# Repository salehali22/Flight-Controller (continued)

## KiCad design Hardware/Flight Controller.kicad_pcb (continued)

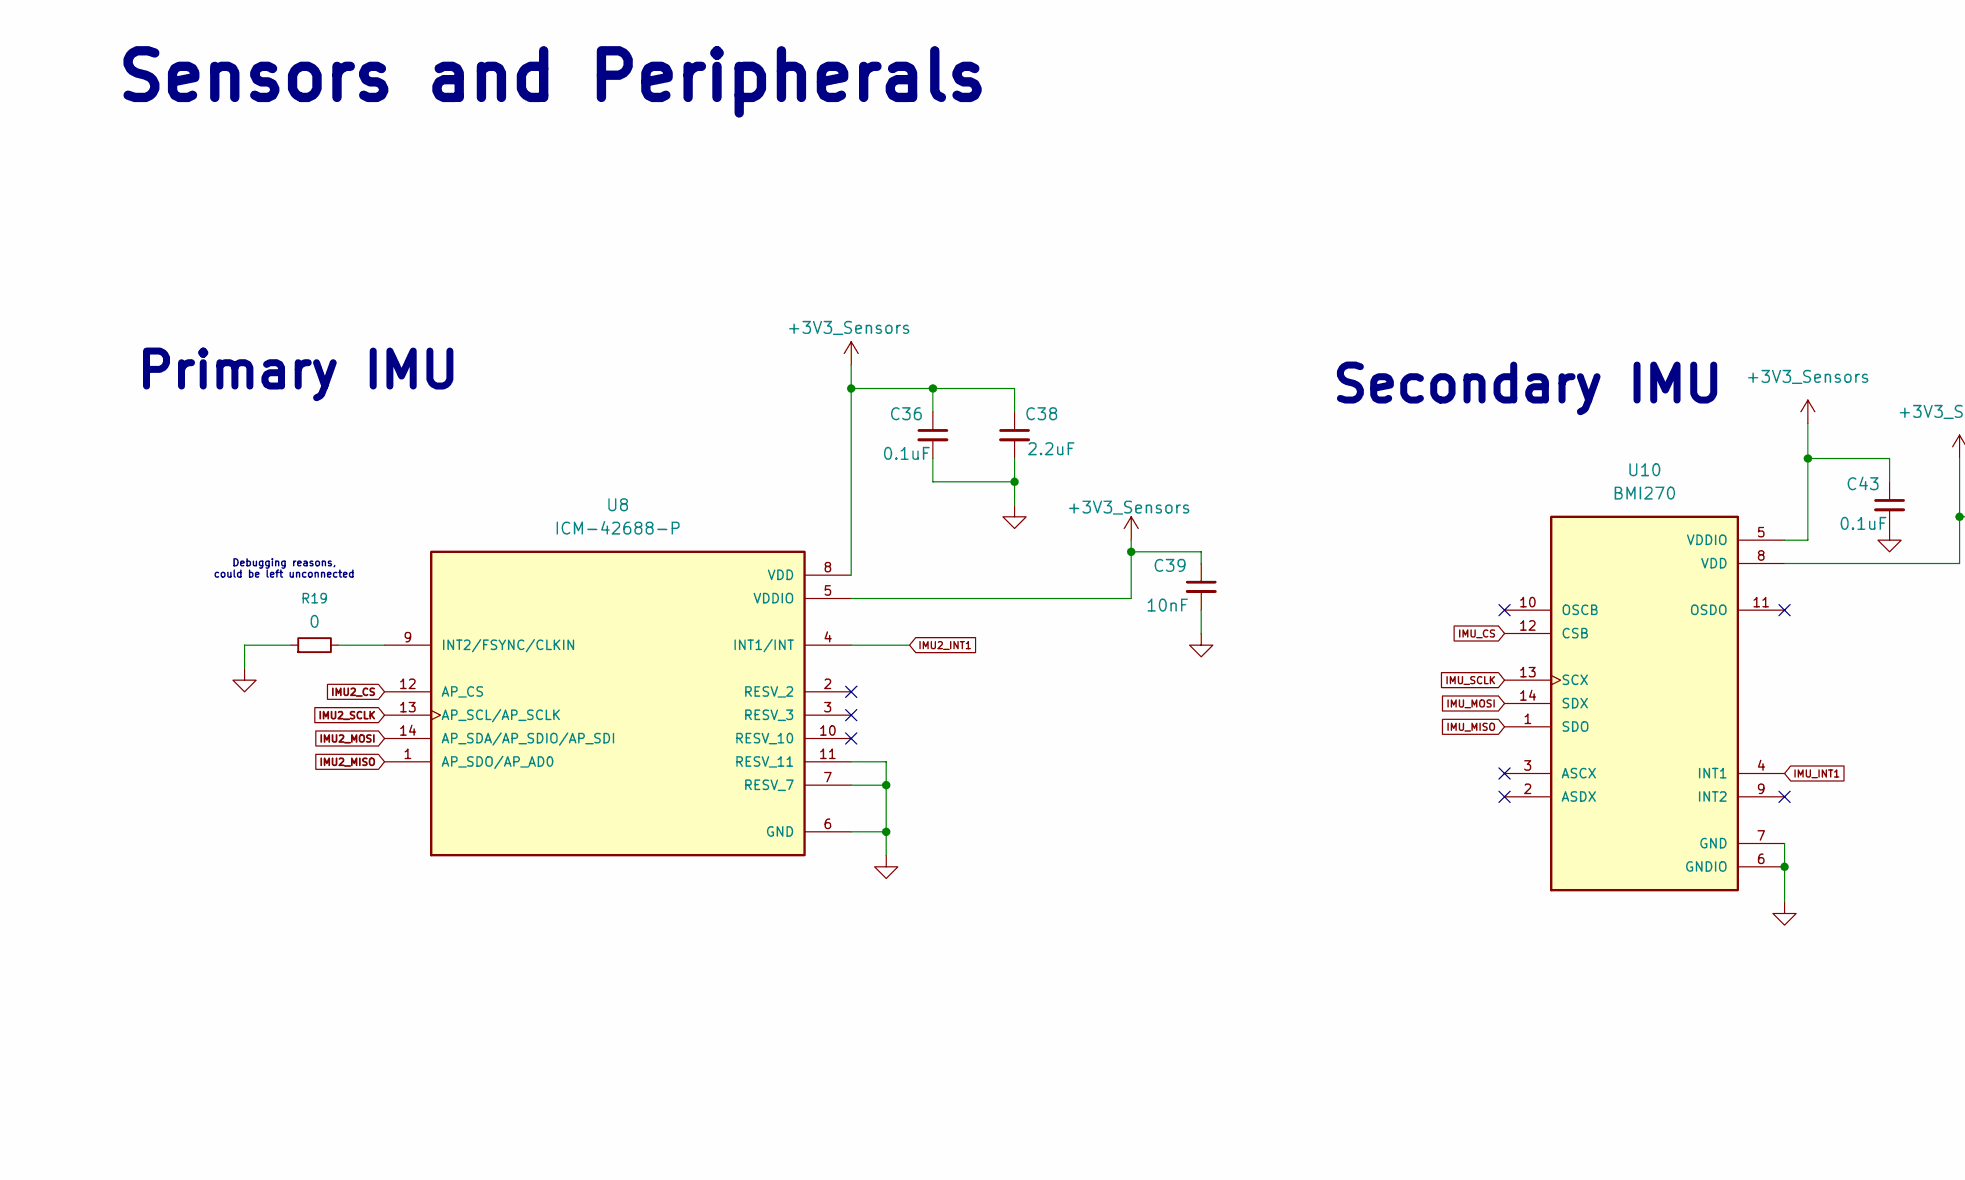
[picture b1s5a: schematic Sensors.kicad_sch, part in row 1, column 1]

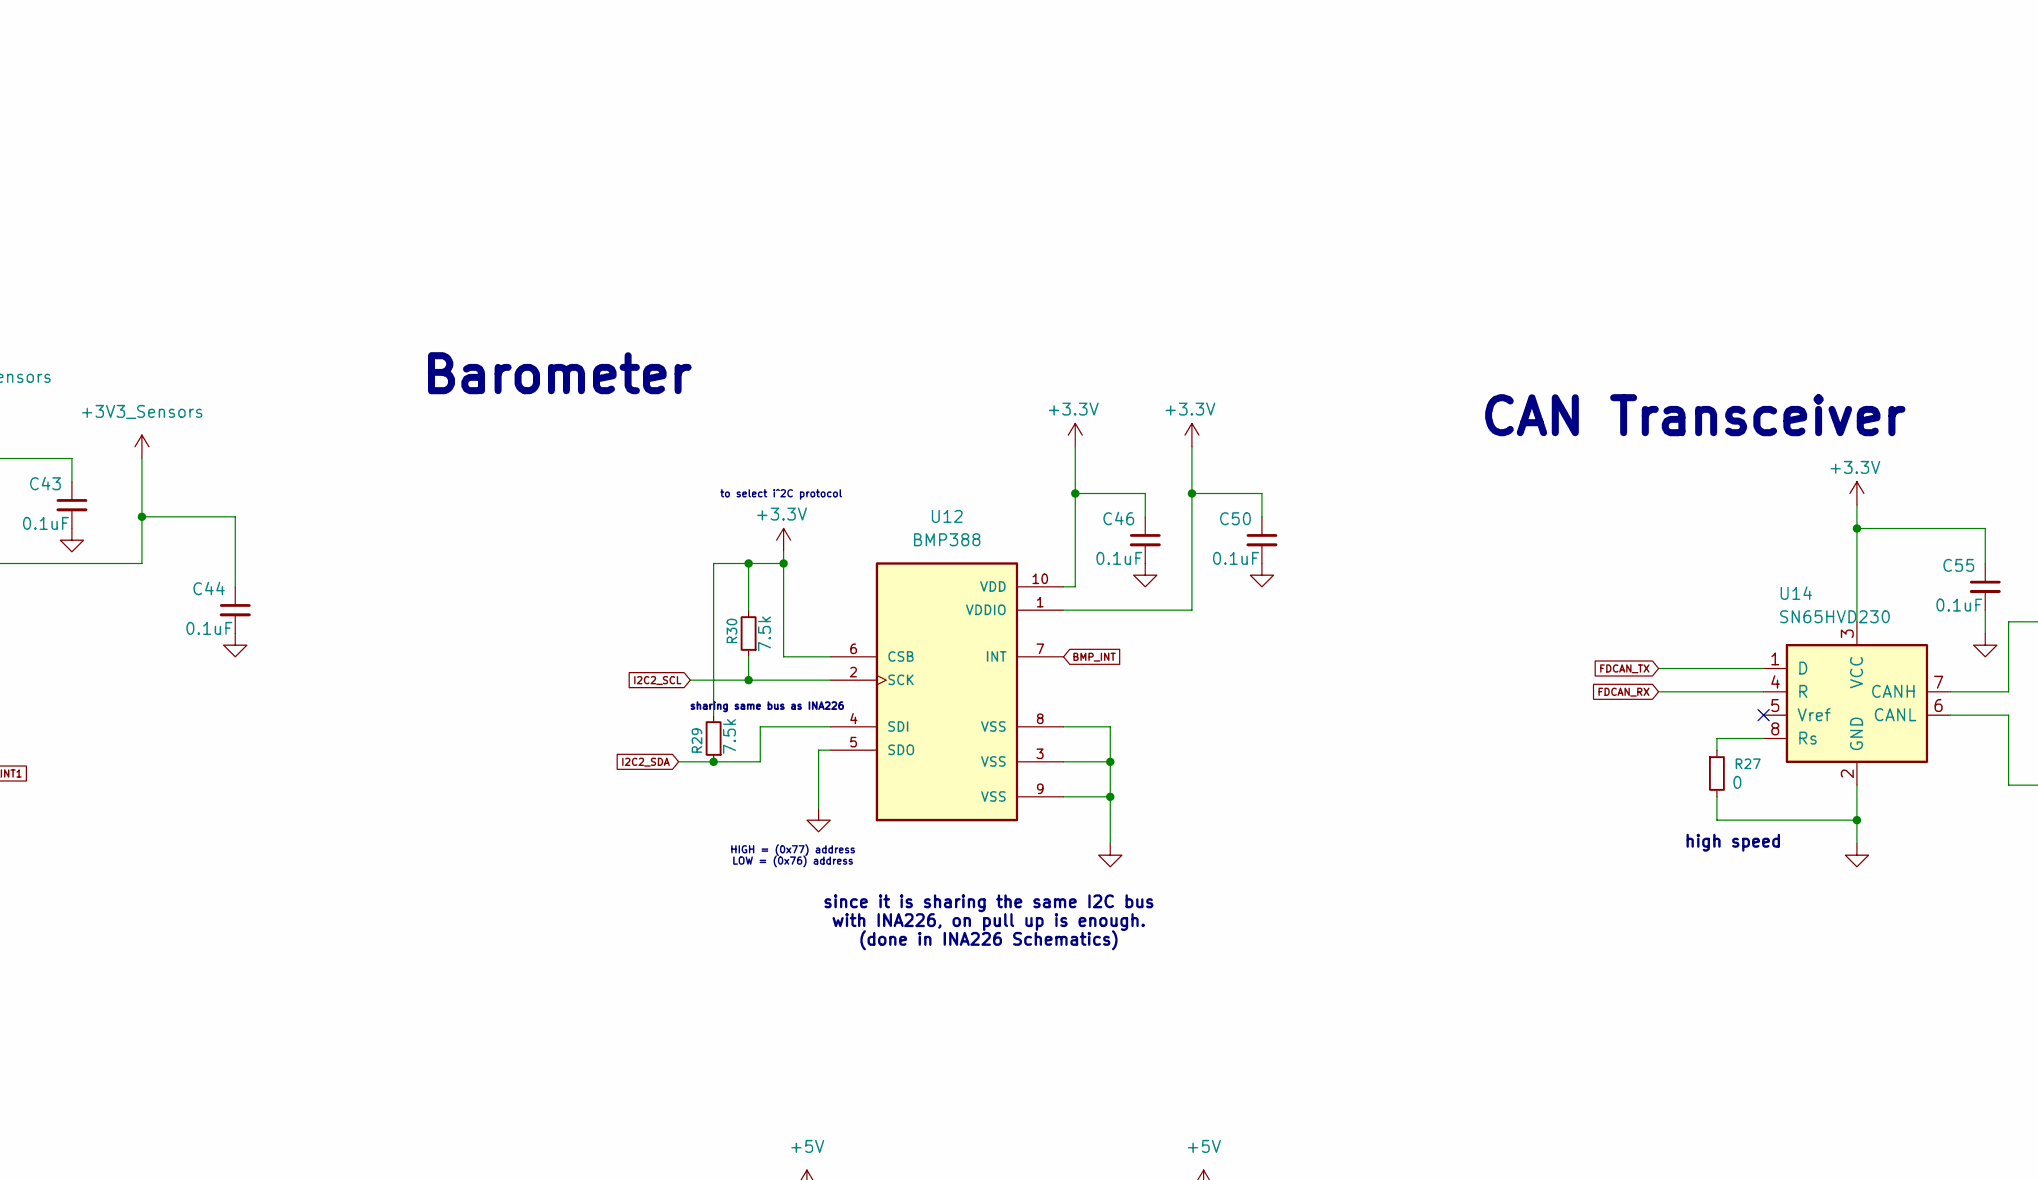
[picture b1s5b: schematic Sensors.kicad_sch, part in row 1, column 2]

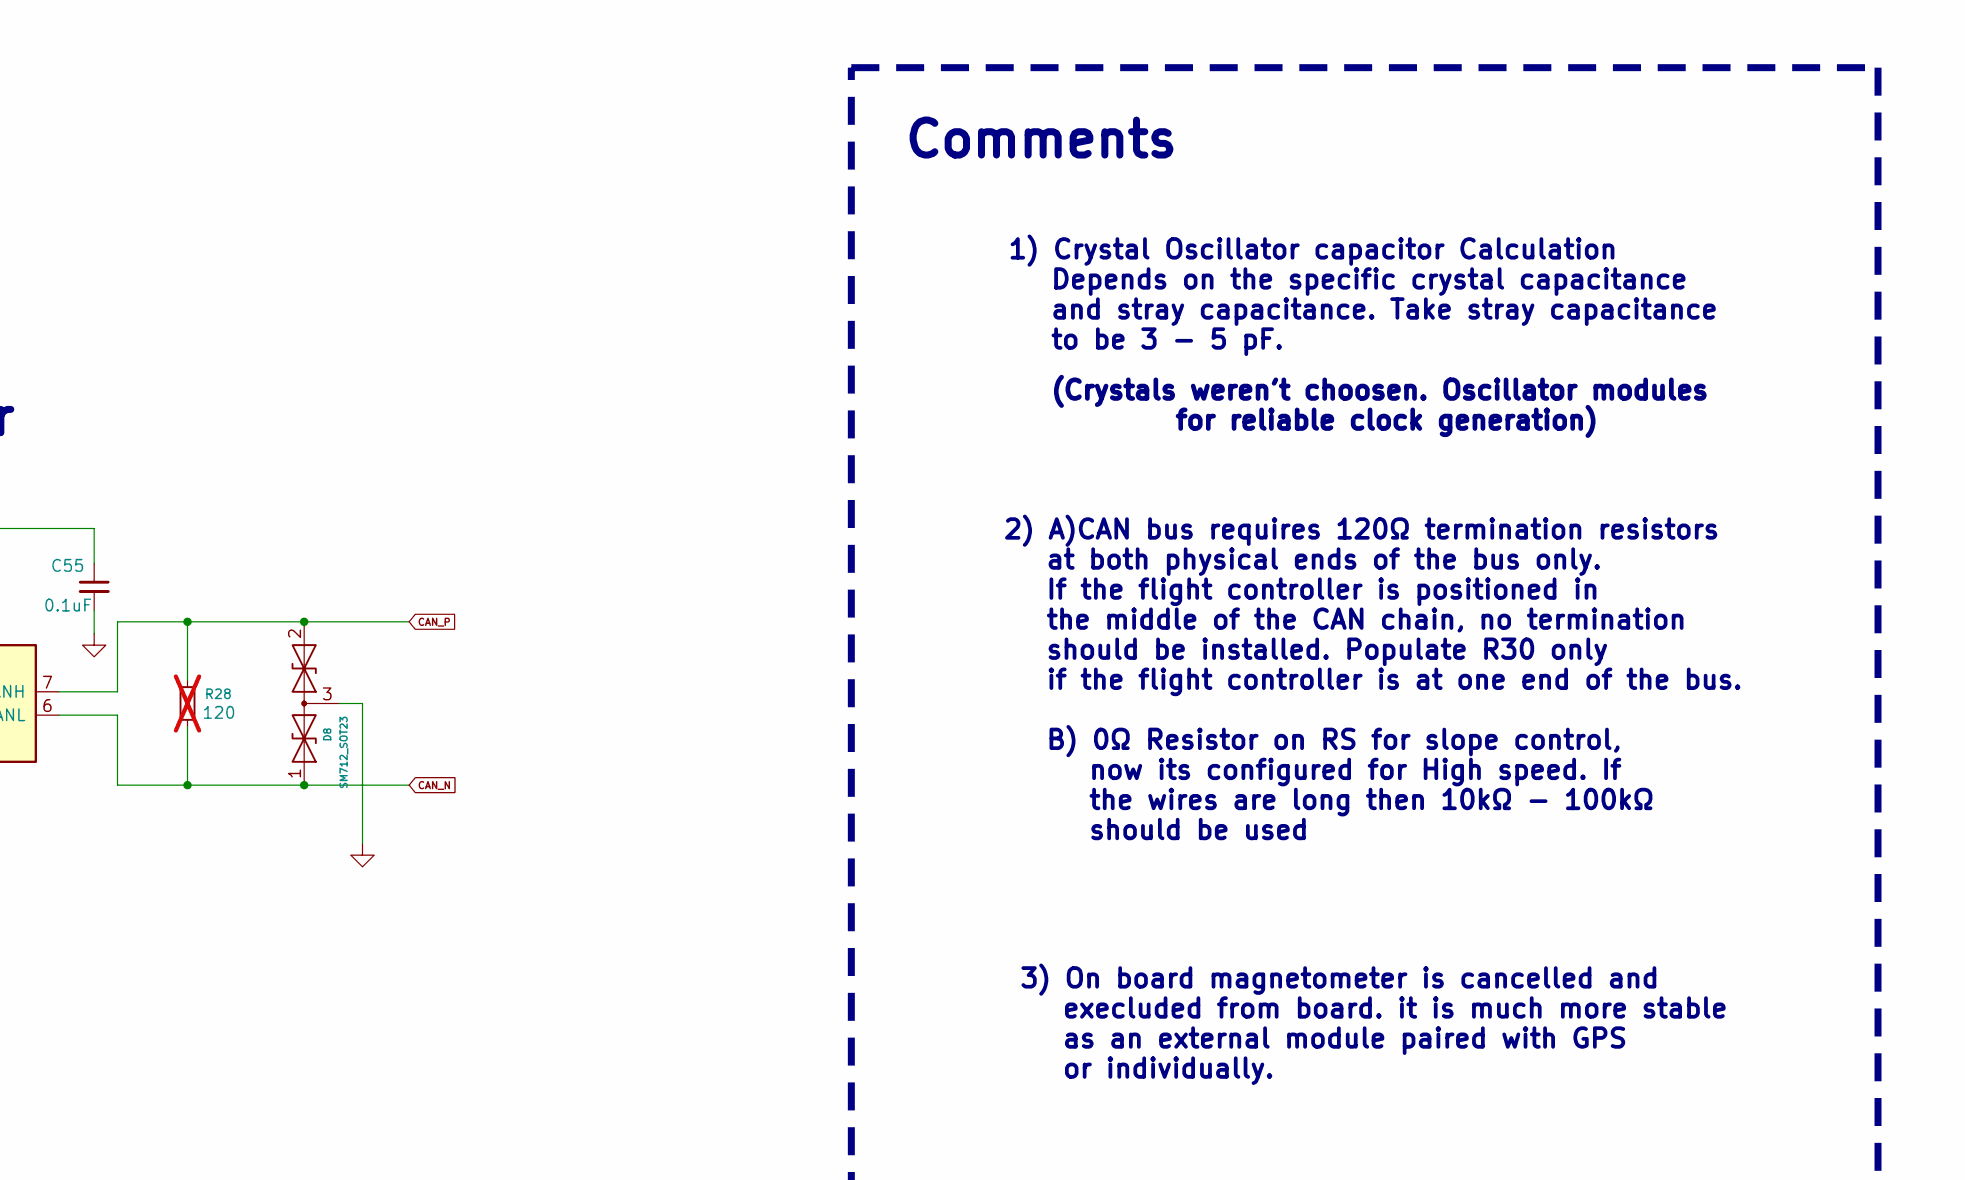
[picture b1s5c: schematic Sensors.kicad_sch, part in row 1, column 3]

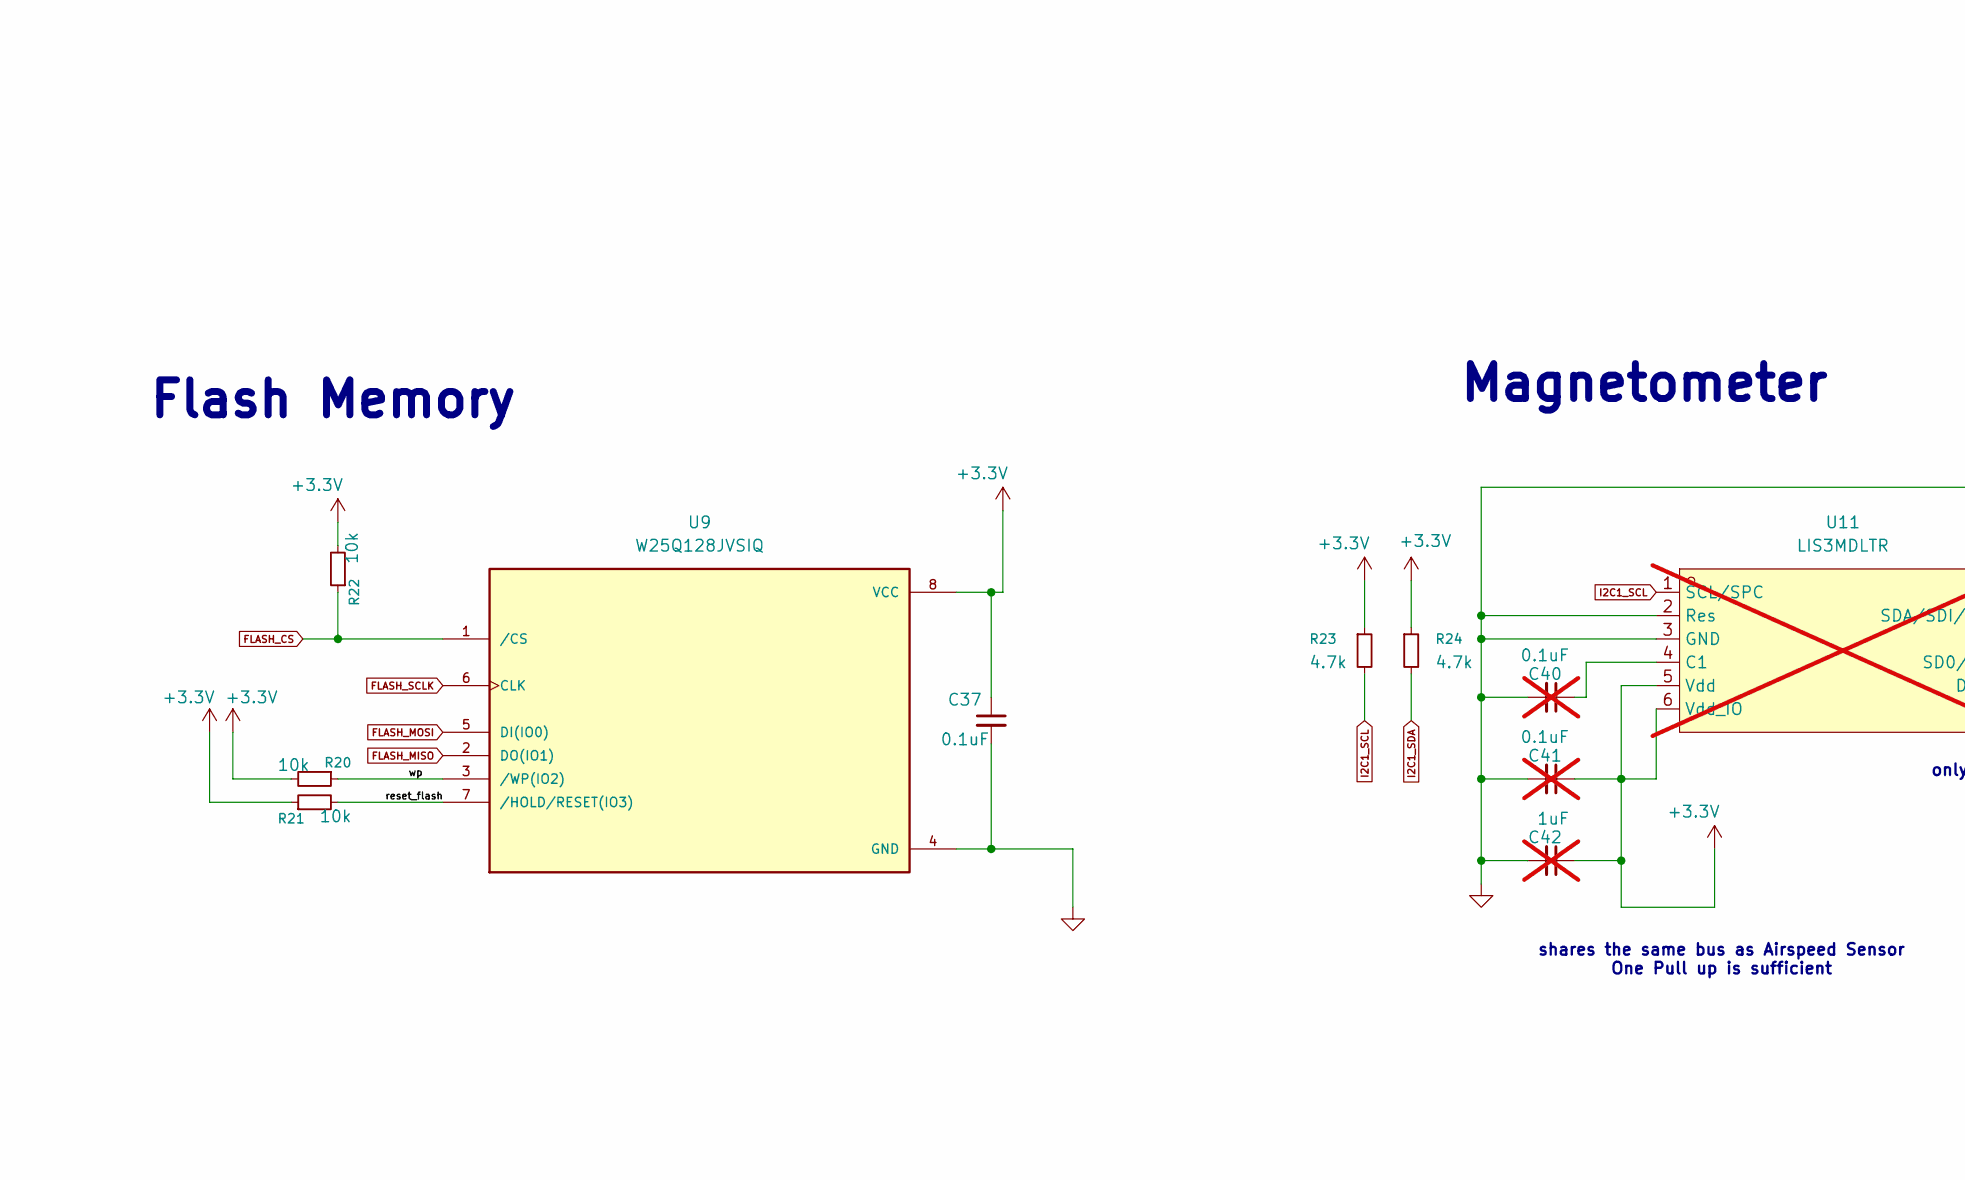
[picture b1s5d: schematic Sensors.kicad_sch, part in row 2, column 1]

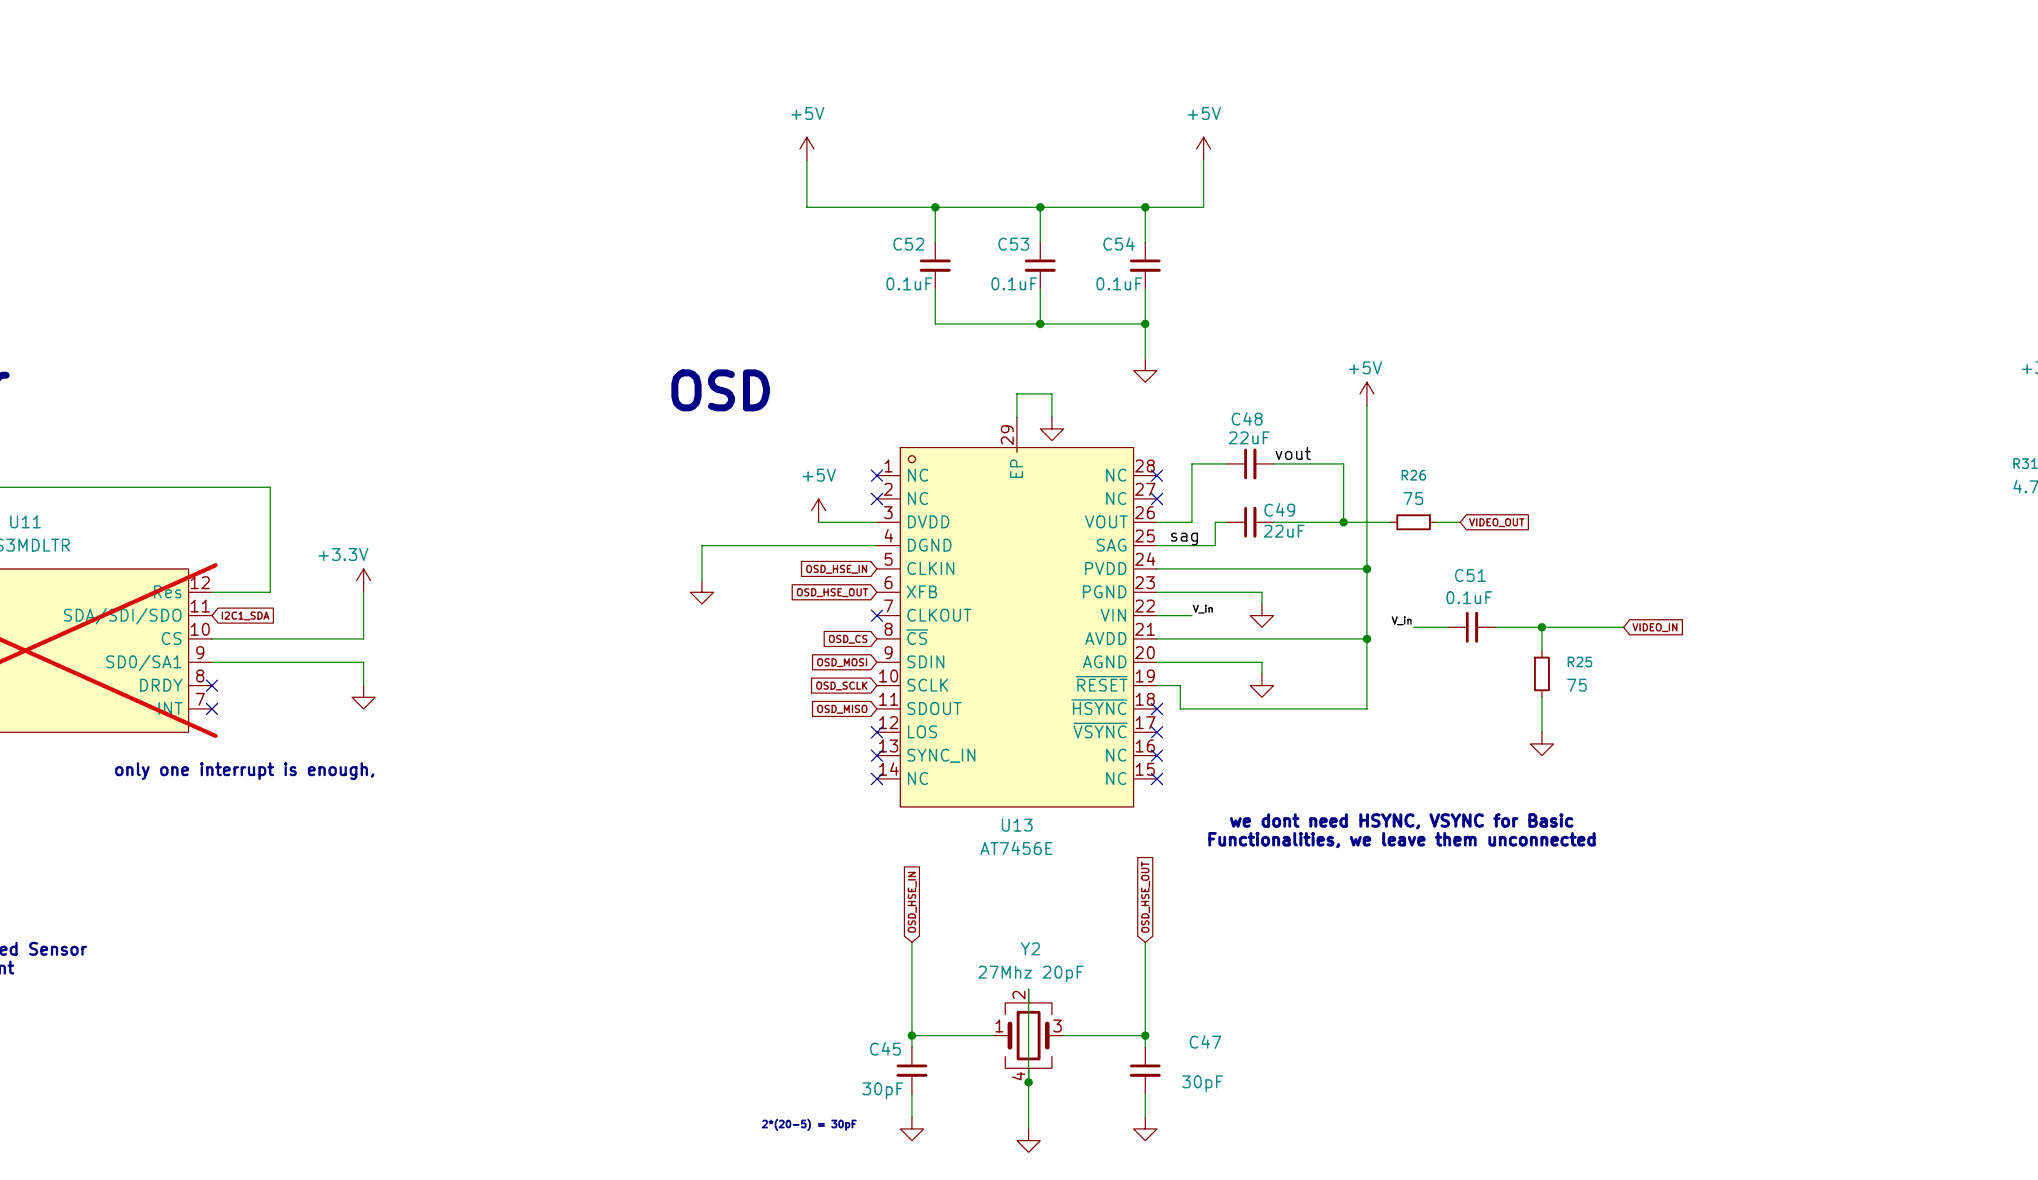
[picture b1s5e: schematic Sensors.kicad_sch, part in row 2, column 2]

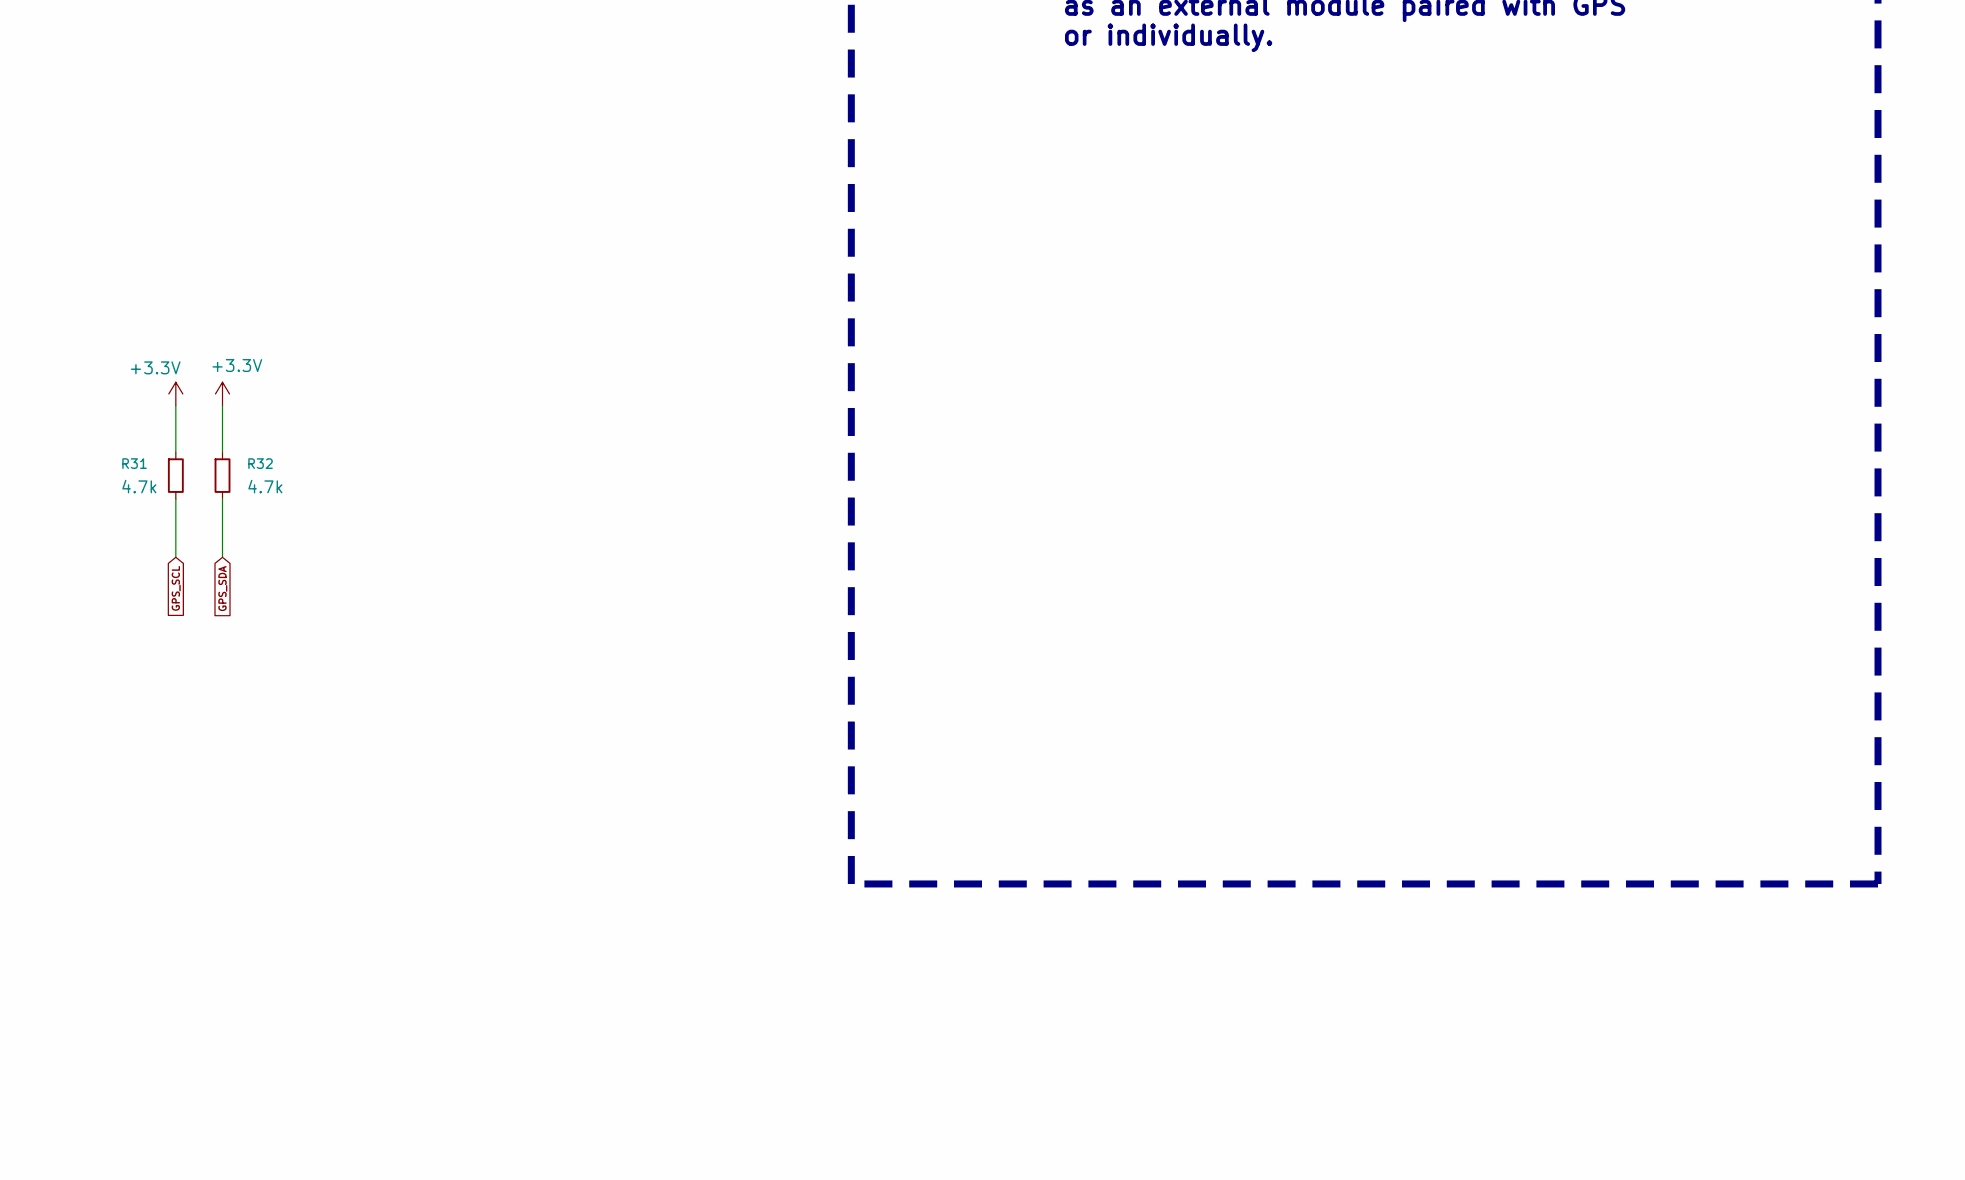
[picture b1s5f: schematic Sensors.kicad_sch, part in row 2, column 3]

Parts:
C36, C37, C43, C44, C46, C50, C51, C52, C53, C54, C55: 0.1uF; C_0402_1005Metric
C38: 2.2uF; C_0603_1608Metric
C39: 10nF; C_0402_1005Metric
C40, C41: 0.1uF; C_0402_1005Metric; not fitted
C42: 1uF; C_0402_1005Metric; not fitted
C45, C47: 30pF; C_0402_1005Metric
C48, C49: 22uF; C_0603_1608Metric
D8: SM712_SOT23; SOT-23
R19, R27: 0; R_0402_1005Metric
R20, R21, R22: 10k; R_0402_1005Metric
R23, R24, R31, R32: 4.7k; R_0402_1005Metric
R25, R26: 75; R_0402_1005Metric
R28: 120; R_0402_1005Metric; not fitted
R29, R30: 7.5k; R_0402_1005Metric
U8: ICM-42688-P; PQFN50P300X250X97-14N; PARTREV 1.2
U9: W25Q128JVSIQ; PARTREV I
U10: BMI270; XDCR_BMI270
U11: LIS3MDLTR; (mag)LGA-12_L2.0-W2.0-P0.50-BL; LCSC Part C478483; not fitted
U12: BMP388; PQFN50P200X200X80-10N; PARTREV 1.1
U13: AT7456E; LCSC Part C82351
U14: SN65HVD230; SOIC-8_3.9x4.9mm_P1.27mm
Y2: 27Mhz 20pF; Crystal_SMD_3225-4Pin_3.2x2.5mm

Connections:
+3.3V: C37.1, C41.1, C42.1, C46.1, C50.1, C55.1, R20.2, R21.1, R22.2, R23.1, R24.1, R29.2, R30.2, R31.1, R32.1, U9.8 (VCC), U11.5 (Vdd), U11.6 (Vdd_IO), U11.10 (CS), U12.1 (VDDIO), U12.6 (CSB), U12.10 (VDD), U14.3 (VCC); also elsewhere on the board
+3V3_Sensors: C36.1, C38.1, C39.1, C43.1, C44.1, U8.5 (VDDIO), U8.8 (VDD), U10.5 (VDDIO), U10.8 (VDD); also elsewhere on the board
+5V: C52.1, C53.1, C54.1, U13.3 (DVDD), U13.19 (~RESET), U13.21 (AVDD), U13.24 (PVDD); also elsewhere on the board
/Sensors and Peripherals/V_in: C51.1, U13.22 (VIN)
/Sensors and Peripherals/reset_flash: R21.2, U9.7 (/HOLD/RESET(IO3))
/Sensors and Peripherals/sag: C49.1, U13.25 (SAG)
/Sensors and Peripherals/vout: C48.2, C49.2, R26.2
/Sensors and Peripherals/wp: R20.1, U9.3 (/WP(IO2))
BMP_INT: U12.7 (INT); also elsewhere on the board
CAN_N: D8.1 (A1), R28.2, U14.6 (CANL); also elsewhere on the board
CAN_P: D8.2 (A2), R28.1, U14.7 (CANH); also elsewhere on the board
FDCAN_RX: U14.4 (R); also elsewhere on the board
FDCAN_TX: U14.1 (D); also elsewhere on the board
FLASH_CS: R22.1, U9.1 (/CS); also elsewhere on the board
FLASH_MISO: U9.2 (DO(IO1)); also elsewhere on the board
FLASH_MOSI: U9.5 (DI(IO0)); also elsewhere on the board
FLASH_SCLK: U9.6 (CLK); also elsewhere on the board
GND: C36.2, C37.2, C38.2, C39.2, C40.2, C41.2, C42.2, C43.2, C44.2, C45.2, C46.2, C47.2, C50.2, C52.2, C53.2, C54.2, C55.2, D8.3 (common), R19.1, R25.2, R27.2, U8.6 (GND), U8.7 (RESV_7), U8.11 (RESV_11), U9.4 (GND), U10.6 (GNDIO), U10.7 (GND), U11.2 (Res), U11.3 (GND), U11.9 (SD0/SA1), U11.12 (Res), U12.3 (VSS), U12.5 (SDO), U12.8 (VSS), U12.9 (VSS), U13.4 (DGND), U13.20 (AGND), U13.23 (PGND), U13.29 (EP), U14.2 (GND), Y2.2, Y2.4; also elsewhere on the board
GPS_SCL: R31.2; also elsewhere on the board
GPS_SDA: R32.2; also elsewhere on the board
I2C1_SCL: R23.2, U11.1 (SCL/SPC); also elsewhere on the board
I2C1_SDA: R24.2, U11.11 (SDA/SDI/SDO); also elsewhere on the board
I2C2_SCL: R30.1, U12.2 (SCK); also elsewhere on the board
I2C2_SDA: R29.1, U12.4 (SDI); also elsewhere on the board
IMU2_CS: U8.12 (AP_CS); also elsewhere on the board
IMU2_INT1: U8.4 (INT1/INT); also elsewhere on the board
IMU2_MISO: U8.1 (AP_SDO/AP_AD0); also elsewhere on the board
IMU2_MOSI: U8.14 (AP_SDA/AP_SDIO/AP_SDI); also elsewhere on the board
IMU2_SCLK: U8.13 (AP_SCL/AP_SCLK); also elsewhere on the board
IMU_CS: U10.12 (CSB); also elsewhere on the board
IMU_INT1: U10.4 (INT1); also elsewhere on the board
IMU_MISO: U10.1 (SDO); also elsewhere on the board
IMU_MOSI: U10.14 (SDX); also elsewhere on the board
IMU_SCLK: U10.13 (SCX); also elsewhere on the board
unnamed: C40.1, U11.4 (C1)
unnamed: R19.2, U8.9 (INT2/FSYNC/CLKIN)
unnamed: C48.1, U13.26 (VOUT)
unnamed: R27.1, U14.8 (Rs)
OSD_CS: U13.8 (~CS); also elsewhere on the board
OSD_HSE_IN: C45.1, U13.5 (CLKIN), Y2.1
OSD_HSE_OUT: C47.1, U13.6 (XFB), Y2.3
OSD_MISO: U13.11 (SDOUT); also elsewhere on the board
OSD_MOSI: U13.9 (SDIN); also elsewhere on the board
OSD_SCLK: U13.10 (SCLK); also elsewhere on the board
VIDEO_IN: C51.2, R25.1; also elsewhere on the board
VIDEO_OUT: R26.1; also elsewhere on the board

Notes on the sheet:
Debugging reasons, could be left unconnected
shares the same bus as Airspeed Sensor One Pull up is sufficient
high speed
we dont need HSYNC, VSYNC for Basic Functionalities, we leave them unconnected
sharing same bus as INA226
(Crystals weren't choosen. Oscillator modules for reliable clock generation)
2*(20-5) = 30pF
1) Crystal Oscillator capacitor Calculation Depends on the specific crystal capacitance and stray capacitance. Take stray capacitance to be 3 - 5 pF.
HIGH = (0x77) address LOW = (0x76) address
to select i^2C protocol
only one interrupt is enough,
Magnetometer
2) A)CAN bus requires 120Ω termination resistors at both physical ends of the bus only. If the flight controller is positioned in the middle of the CAN chain, no termination should be installed. Populate R30 only if the flight controller is at one end of the bus. B) 0Ω Resistor on RS for slope cont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
Barometer
Flash Memory
3) On board magnetometer is cancelled and execluded from board. it is much more stable as an external module paired with GPS or individually.
OSD
Comments
Secondary IMU
Primary IMU
CAN Transceiver
Sensors and Peripherals
since it is sharing the same I2C bus with INA226, on pull up is enough. (done in INA226 Schematics)

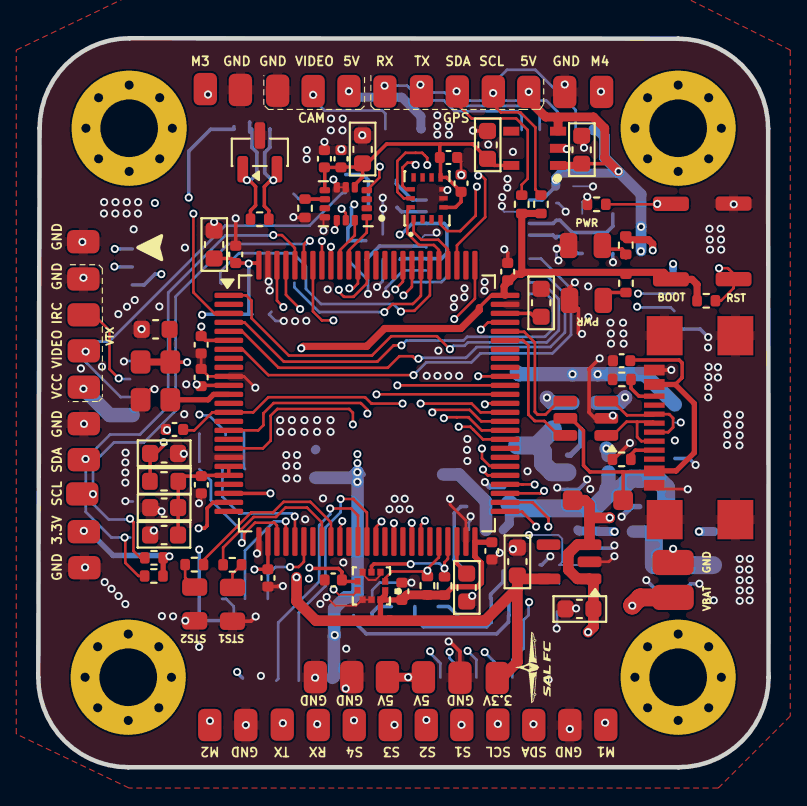
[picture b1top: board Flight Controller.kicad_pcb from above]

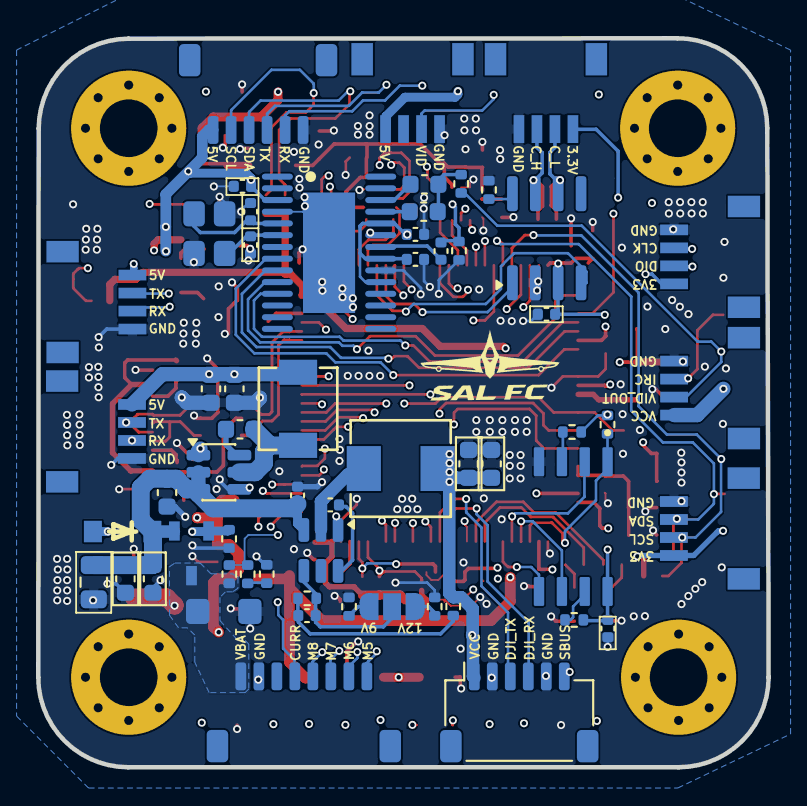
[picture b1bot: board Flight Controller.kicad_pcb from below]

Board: 6 copper layers, 40.6 x 40.5 mm, 165 parts (58 on the bottom side), 105 nets.

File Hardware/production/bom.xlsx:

Designator | Footprint | Quantity | Value | LCSC Part #
C1, C10, C3 | 603 | 3 | 10uF
C14, C33 | 603 | 2 | 0.1uF
C15, C16, C48, C49, C6, C7 | 603 | 6 | 22uF
C17, C18, C20, C23, C27 | 603 | 5 | 1uF
C19 | 603 | 1 | 4,7uF
C2, C24, C25, C26, C28, C29, C31, C32, C36, C37, C43, C44, C46, C5, C50, C51, C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 | 402 | 20 | 0.1uF
C21 | 603 | 1 | 10nF
C22 | 603 | 1 | 4.7uF
C30, C39 | 402 | 2 | 10nF
C34, C35, C38 | 603 | 3 | 2.2uF
C4 | 805 | 1 | 22uF
C45, C47 | 402 | 2 | 30pF
C8 | 402 | 1 | 75pF
C9 | 402 | 1 | 4.7uF
D1 | D_SMF | 1 | SMF26A
D2 | (zener)SOD-123F_L2.8-W1.8-LS3.7-RD | 1 | BZT52C12-13-F | C177013
D3 | D_SOD-123F | 1 | PMEG2010EH
D4, D5, D6, D7 | 805 | 4 | LED
D8 | SOT-23 | 1 | SM712_SOT23
FB1 | 603 | 1 | 1k@100Mhz
H1, H2, H3, H4 | MountingHole_3.2mm_M3_Pad_Via | 4 | MountingHole
J1 | GCT_USB4110GFA | 1 | USB4110GFA
J10, J11 | CONN-SMD_4P-P1.00_SM04B-SRSS-TB-LF-SN | 2 | CAN BUS
J2 | CONN-SMD_4P-P1.00_SM04B-SRSS-TB-LF-SN | 1 | FPV
J3 | CONN-SMD_4P-P1.00_SM04B-SRSS-TB-LF-SN | 1 | ST_LINK
J4 | JST_SH_SM06B-SRSS-TB_1x06-1MP_P1.00mm_Horizontal | 1 | GPS
J5 | CONN-SMD_4P-P1.00_SM04B-SRSS-TB-LF-SN | 1 | Airspeed sensor
J6 | JST_SH_SM08B-SRSS-TB_1x08-1MP_P1.00mm_Horizontal | 1 | 4in1 ESC
J7 | CONN-SMD_4P-P1.00_SM04B-SRSS-TB-LF-SN | 1 | RC Receiver
J8 | CONN-SMD_4P-P1.00_SM04B-SRSS-TB-LF-SN | 1 | VTX
J9 | JST_SH_SM06B-SRSS-TB_1x06-1MP_P1.00mm_Horizontal | 1 | DJI
L1 | IND-SMD_L5.4-W5.2 | 1 | 15uH
L2 | IND-SMD_L4.4-W4.2 | 1 | 4.7uH
Q1 | AO3407A | 1 | AO3407A | C15155
R1, R2 | 402 | 2 | 5.1k
R13, R14, R17, R18 | 402 | 4 | 330
R15, R16, R20, R21, R22 | 402 | 5 | 10k
R19, R27, R8 | 402 | 3 | 0
R23, R24, R31, R32 | 402 | 4 | 4.7k
R25, R26 | 402 | 2 | 75
R29, R30 | 402 | 2 | 7.5k
R3, R5 | 402 | 2 | 100k
R4 | 402 | 1 | 49.9
R5B1 | 402 | 1 | 7.15K
R5C1 | 402 | 1 | 5.23k
R6 | 402 | 1 | 4.42k
R7 | 402 | 1 | 20k
SW1 | SW_Push_SPST_NO_Alps_SKRK | 1 | reset
SW2 | SW_Push_SPST_NO_Alps_SKRK | 1 | MCU_BOOT
TP1, TP10, TP12, TP17, TP18, TP21, TP22, TP25, TP26, TP27, TP4, TP43, TP45, TP6 | Solderpad | 14 | power
TP13, TP16, TP20, TP24 | Solderpad | 4 | servos
TP14, TP23 | BAT pad | 2 | power
TP15 | Solderpad | 1 | M4
TP2 | Solderpad | 1 | Motor 1
TP28, TP33, TP34, TP35, TP36, TP37, TP38, TP39, TP40, TP41, TP42 | Solderpad | 11 | sensors
TP29 | Solderpad | 1 | TELEMETRY_RX
TP3, TP32, TP7, TP9 | Solderpad | 4 | GND
TP30 | Solderpad | 1 | TELEMETRY_TX
TP31 | Solderpad | 1 | 5V
TP5 | Solderpad | 1 | Motor 2
TP8 | Solderpad | 1 | M3
U1 | SOT-23-6 | 1 | TPS54302
U10 | XDCR_BMI270 | 1 | BMI270
U12 | PQFN50P200X200X80-10N | 1 | BMP388
U13 | AT7456E | 1 | AT7456E | C82351
U14 | SOIC-8_3.9x4.9mm_P1.27mm | 1 | SN65HVD230
U2 | SOT-23-6 | 1 | USBLC6-2SC6
U4 | TSOT-23-6 | 1 | AP63205WU
U5 | SOT-23-5 | 1 | AP2112K-3.3
U6 | (AP7343 )SOT-25_L3.0-W1.6-P0.95-LS2.8-BL | 1 | AP7343-33W5-7 | C460383
U7 | LQFP-100_14x14mm_P0.5mm | 1 | STM32H743VITx
U8 | PQFN50P300X250X97-14N | 1 | ICM-42688-P
U9 | W25Q128JVSIQ | 1 | W25Q128JVSIQ
Y1 | Oscillator_SMD_Abracon_ASE-4Pin_3.2x2.5mm | 1 | ASE-8.000MHZ-LC-T
Y2 | Crystal_SMD_3225-4Pin_3.2x2.5mm | 1 | 27Mhz 20pF
